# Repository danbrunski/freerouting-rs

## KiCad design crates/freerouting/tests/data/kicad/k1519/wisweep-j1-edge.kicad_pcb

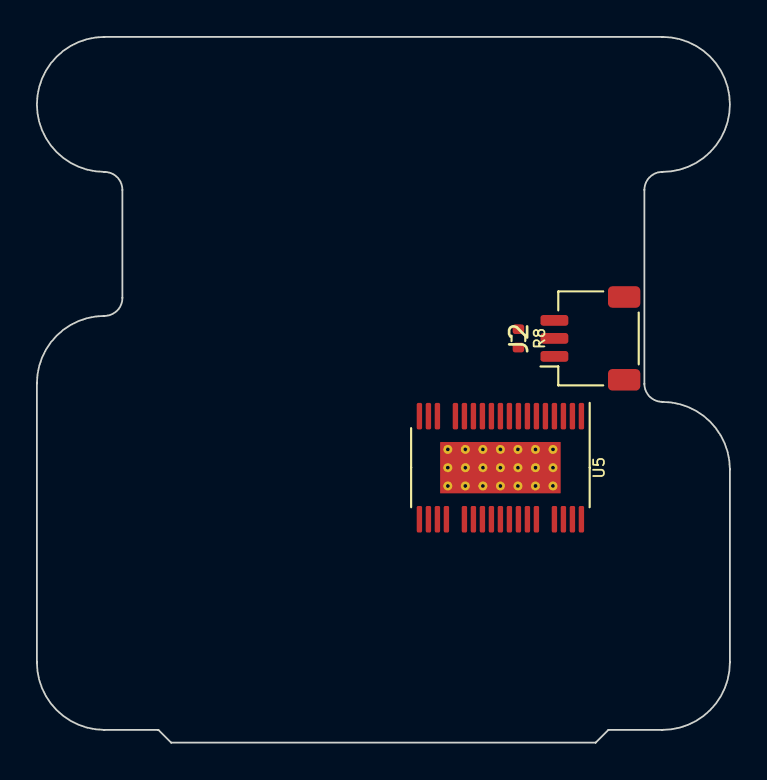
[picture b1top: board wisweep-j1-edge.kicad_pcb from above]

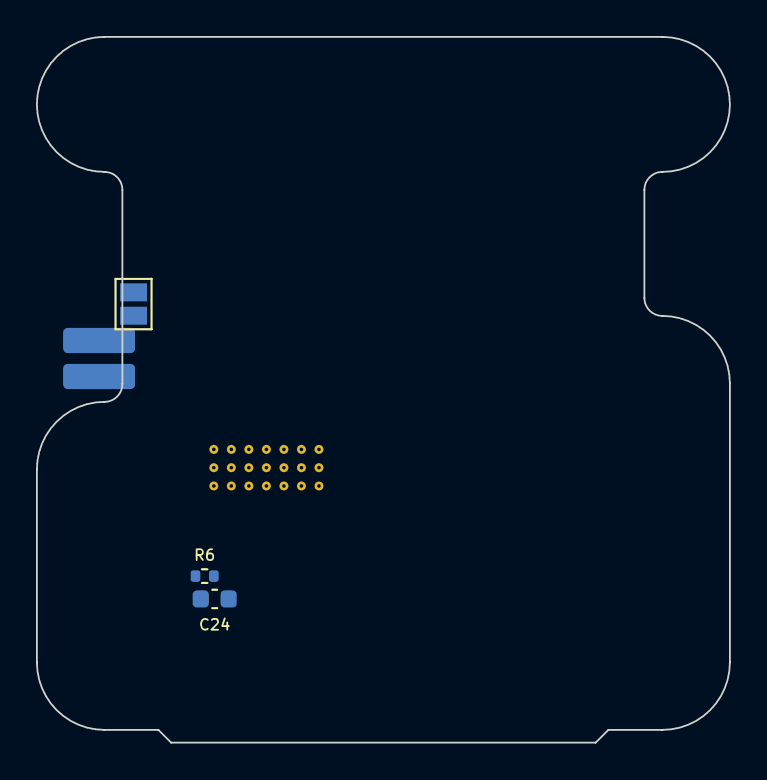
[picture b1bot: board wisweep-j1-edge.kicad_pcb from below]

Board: 4 copper layers, 38.5 x 39.2 mm, 7 parts (4 on the bottom side), 5 nets, no tracks yet.

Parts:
C24: 100nF; C_0603_1608Metric
J1: Conn_01x02; PinHeader_1x02_P2.00mm_Vertical_SMD_Pin1Left
J2: Conn_01x03; JST_SH_SM03B-SRSS-TB_1x03-1MP_P1.00mm_Horizontal
JP3: Jumper_2_Open; SolderJumper-2_P1.3mm_Open_Pad1.0x1.5mm
R6, R8: 10k; R_0402_1005Metric
U5: TMC5240-TSSOP38; TSSOP-38_4.4x9.7mm_P0.5mm

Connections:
+3V3: J2.2, R6.2, R8.2, U5.11 (VCC_IO)
/TMC_AIN: C24.2, J1.2, R6.1, U5.8 (AIN)
/TMC_REFL: J2.3, JP3.2 (B), R8.1, U5.5 (REFL)
GND: C24.1, J1.1, J2.1, U5.3 (CLK), U5.10 (AGND), U5.27 (PGND1), U5.31 (PGND2), U5.39 (EP)
VM: U5.25 (VS1), U5.29 (VS2), U5.33 (VS3), U5.35 (SLEEP)
